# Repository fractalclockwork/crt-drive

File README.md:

# crt-drive

Programmable CRT drive: sync and video from a microcontroller for analog CRTs and TVs.

The first target is the Link MC5 terminal (Wyse WY-120 architecture). A Raspberry Pi Pico (RP2040) replaces the CRT drive ASIC (Wyse 211009-02, U4): it synthesizes active-low `/HSYNC` and `/VSYNC` plus active-high dual video (V0 dim, V1 normal) and drives the existing deflection and neck boards. The original CPU, EPROM, and VRAM bus do not need to run.

**Status:** Injection pads and the Pico + 74AHCT125 carrier (KiCad protoboard) are decided. The Dev-Host Docker toolchain is validated (`make smoke` / `make test APP=hello`). **Default firmware is the 60 Hz 80-col measure pattern** (`make build` / `make flash` / `make test` / `make monitor`): GPIO 0–3, box+grid+plus; USB `m` 80/132-col, `r` 60/78 Hz; `a`/`d`/`w`/`s` nudge H/V phase. Four-mode analog drawings: `make build APP=pattern`. Phosphor reel: `make build APP=demos` (same `m`/`r`). Glass TTY: `make build APP=term`. CRT HIL is in progress after isolation and the 74AHCT125.

## Docs

| Doc | Role |
| --- | --- |
| [Project writeup](docs/project-writeup.md) | Methodology, hardware, software, HIL, camera on the glass |
| [Hardware design](docs/hardware-design.md) | Board identity, labeled pads V0/V1/V/H/GND, level shift, 60 Hz then 78 Hz timings |
| [Firmware plan](docs/firmware-plan.md) | Phased PIO / DMA / framebuffer build, open choices |
| [Test patterns](docs/test-pattern-design.md) | `cross60` HIL record (keep); six 78 Hz drawings still on `APP=pattern` |
| [Terminal emulator](docs/terminal-plan.md) | Glass TTY (`apps/term`, `make build APP=term`) |
| [Video TTY](docs/vtty.md) | Host session (`apps/vtty`, `tools/vtty.py`, news page) |
| [Phosphor demos](docs/demo-plan.md) | Attract reel (`apps/demos`, `make build APP=demos`) |
| [Firmware apps](apps/) | Separate CMake projects: cross60 (default), pattern, term, demos, vtty, rick |
| [Toolchains](docs/toolchains.md) | Dev-Host Docker image, volume mount, USB flash (no gateway) |
| [KiCad project](docs/kicad/crt-drive/) | Pico carrier / level-shift protoboard (schematic + jumper layout) |
| [Injector power](docs/kicad/power_supply.md) | +5 V, VSYS Schottky, AHCT buffer rail |
| [PCB drawing](docs/PCB.svg) | Board artwork referenced from the hardware guide |
| [Signal pads](docs/signals_pcb.png) | Solder-side taps next to U4: V0, V1, V, H, GND |

## Dev-Host toolchain (Docker)

Edit on the Dev-Host. Firmware is compiled by calling into the `pico-dev` image from that host (`make` at the repository root); the repo is bind-mounted at `/workspace` for the call. Plug the Pico into **this** machine (no Raspberry Pi gateway). Modeled on [fractalclockwork/cede](https://github.com/fractalclockwork/cede) `lab/docker/pico-dev`.

**Full guide:** [docs/toolchains.md](docs/toolchains.md) (setup, USB modes, `hello_pico`, troubleshooting). Short path: [`docker/README.md`](docker/README.md).

```bash
make image          # build crt-drive/pico-dev:local
make smoke          # ARM GCC, CMake, Ninja, Pico SDK, picotool USB
make pico-discover  # identify the Pico on this host's USB
make test APP=hello # build, flash, USB CDC ping (hello_pico)
make build          # 60 Hz 80-col plus (default CRT UF2)
make flash          # load crt_cross60
make monitor        # USB CDC; follows whichever app is running
make build APP=pattern
make build APP=term # glass TTY
make build APP=vtty # host session; usage in docs/vtty.md
uv sync             # Dev-Host .venv; Pillow for tools/vtty.py images
make vtty-start     # news page; make vtty-stop frees the serial node
make build APP=demos
make help           # all targets
```

`make shell` and `make shell-usb` are a call into the image. Leave with `exit`. The editor stays on the Dev-Host.

## Phased development

Hardware is ready to drive: lift harness at pads **V0**, **V1**, **V**, **H**, **GND**; level-shift on the Pico carrier (74AHCT125); power from logic-board +5 V / GND. First video mode is **60 Hz 80-col** (32.1 MHz dots, 1024-dot `/HSYNC`, 523 lines); USB `m` is **60 Hz 132-col** (1188×416). **78 Hz** patterns come after that raster is on-glass.

Firmware order (detail in [firmware-plan.md](docs/firmware-plan.md)):

1. Clock + PIO load — Pico PLL; 60 Hz in [`apps/cross60`](apps/cross60/), 78 Hz in [`video/`](video/)
2. Stable `/HSYNC` and `/VSYNC` — 60 Hz wraps 1024 dots / 523 lines (HIL); 78 Hz 1530 / 402 on a scope
3. Pixel SM + packing — 800×416 @ 2 bpp (60 Hz), 800×338 (78 Hz); FIFO stall, trailing off word
4. DMA loop into PIO TX — per-line kick from hsync RX
5. 60 Hz plus — default UF2; center and size on the live CRT (`make test`)
6. 78 Hz test patterns — `make test APP=pattern` after 60 Hz fills
7. Other apps — glass TTY in [`apps/term/`](apps/term/); phosphor reel in [`apps/demos/`](apps/demos/)

## Safety

CRT anode and flyback voltages are lethal. Isolate U4 by lifting the harness wires at the labeled V0, V1, V, H, and GND pads before splicing in RP2040 signals. Do not work on a powered chassis until you know the discharge path for the CRT anode cap.

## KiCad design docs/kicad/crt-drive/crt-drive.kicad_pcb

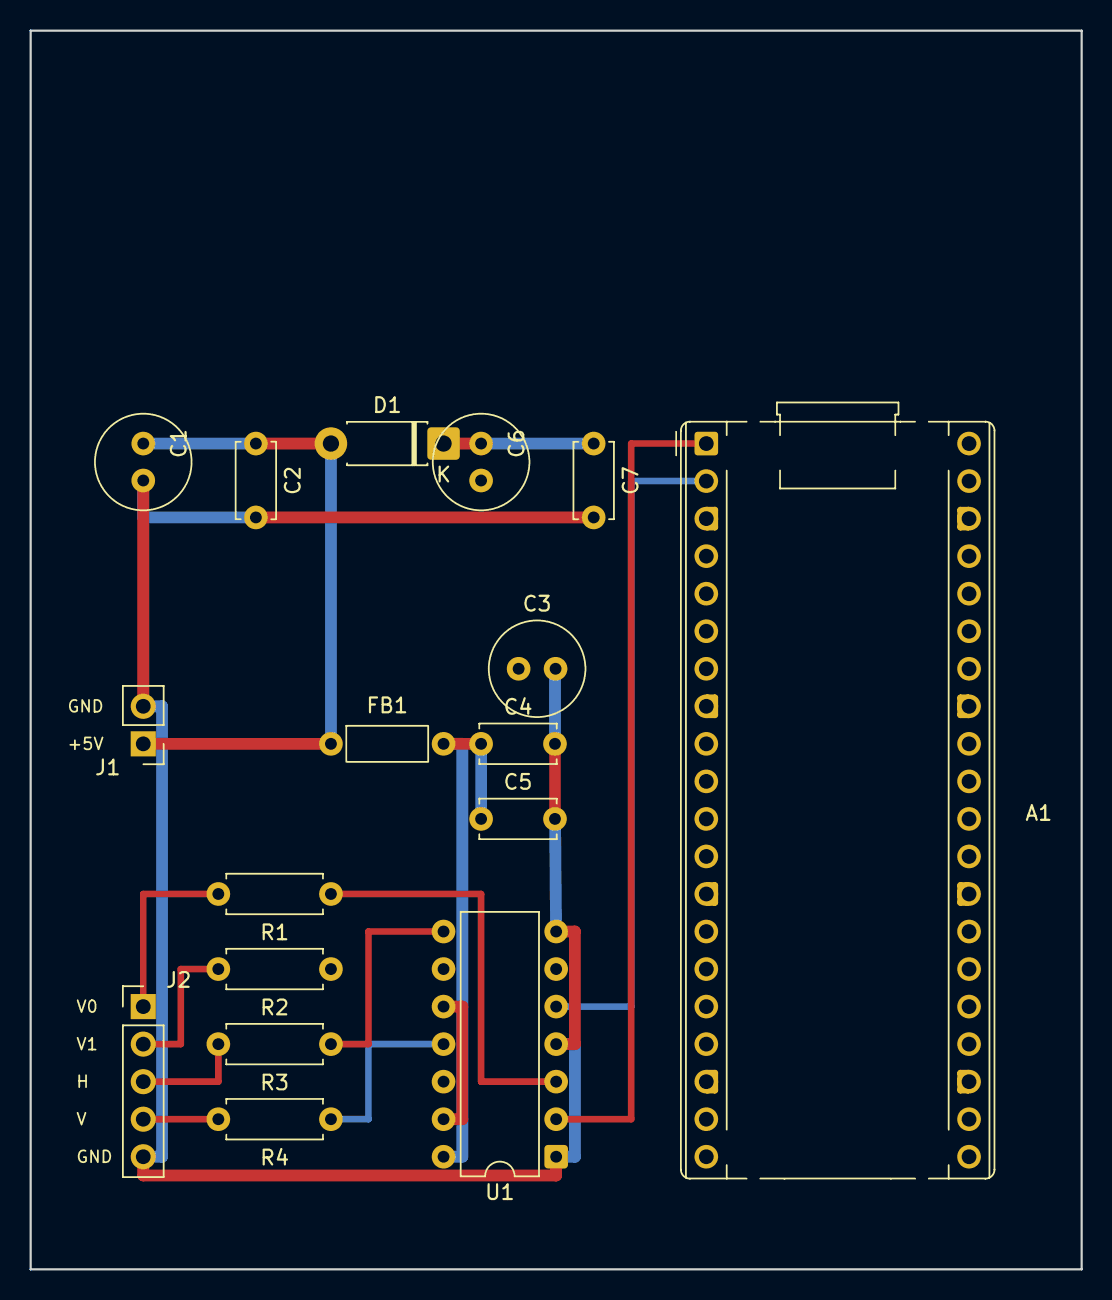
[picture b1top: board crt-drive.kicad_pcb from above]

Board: 8 copper layers, 71.1 x 83.8 mm, 17 parts (0 on the bottom side), 16 nets.

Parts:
A1: RaspberryPi_Pico; RaspberryPi_Pico_Common_THT
C1, C3, C6: 10uF; C_Radial_D6.3mm_H11.0mm_P2.50mm
C2, C4, C7: 100nF; C_Disc_D5.0mm_W2.5mm_P5.00mm
C5: 1nF; C_Disc_D5.0mm_W2.5mm_P5.00mm
D1: 1N5817; D_DO-41_SOD81_P7.62mm_Horizontal
FB1: 100R @ 100MHz; L_Axial_L5.3mm_D2.2mm_P7.62mm_Horizontal_Vishay_IM-1
J1: Logic +5V; PinHeader_1x02_P2.54mm_Vertical
J2: Harness; PinHeader_1x05_P2.54mm_Vertical
R1, R2: 100R; R_Axial_DIN0207_L6.3mm_D2.5mm_P7.62mm_Horizontal
R3, R4: 47R; R_Axial_DIN0207_L6.3mm_D2.5mm_P7.62mm_Horizontal
U1: 74AHCT125; DIP-14_W7.62mm

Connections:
+5V: C1.1, C2.1, D1.2, FB1.1, J1.1
+5V_BUFFER: C3.1, C4.1, C5.1, FB1.2, U1.14
/H: J2.3, R3.2
/V: J2.4, R4.2
/V0: J2.1, R1.2
/V0_3V3: A1.1, U1.2
/V1: J2.2, R2.2
/V1_3V3: A1.2, U1.5
/VSYS: A1.39, C6.1, C7.1, D1.1
/~HSYNC: A1.4, U1.9
/~VSYNC: A1.5, U1.12
GND: A1.3, A1.8, A1.13, A1.18, A1.23, A1.28, A1.33, A1.38, C1.2, C2.2, C3.2, C4.2, C5.2, C6.2, C7.2, J1.2, J2.5, U1.1, U1.4, U1.7, U1.10, U1.13
unnamed: R1.1, U1.3
unnamed: R2.1, U1.6
unnamed: R3.1, U1.8
unnamed: R4.1, U1.11
